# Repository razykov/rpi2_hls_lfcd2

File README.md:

# rpi2_hls_lfcd2
Adapter for connection hls_lfcd2 lidar to RaspberryPi

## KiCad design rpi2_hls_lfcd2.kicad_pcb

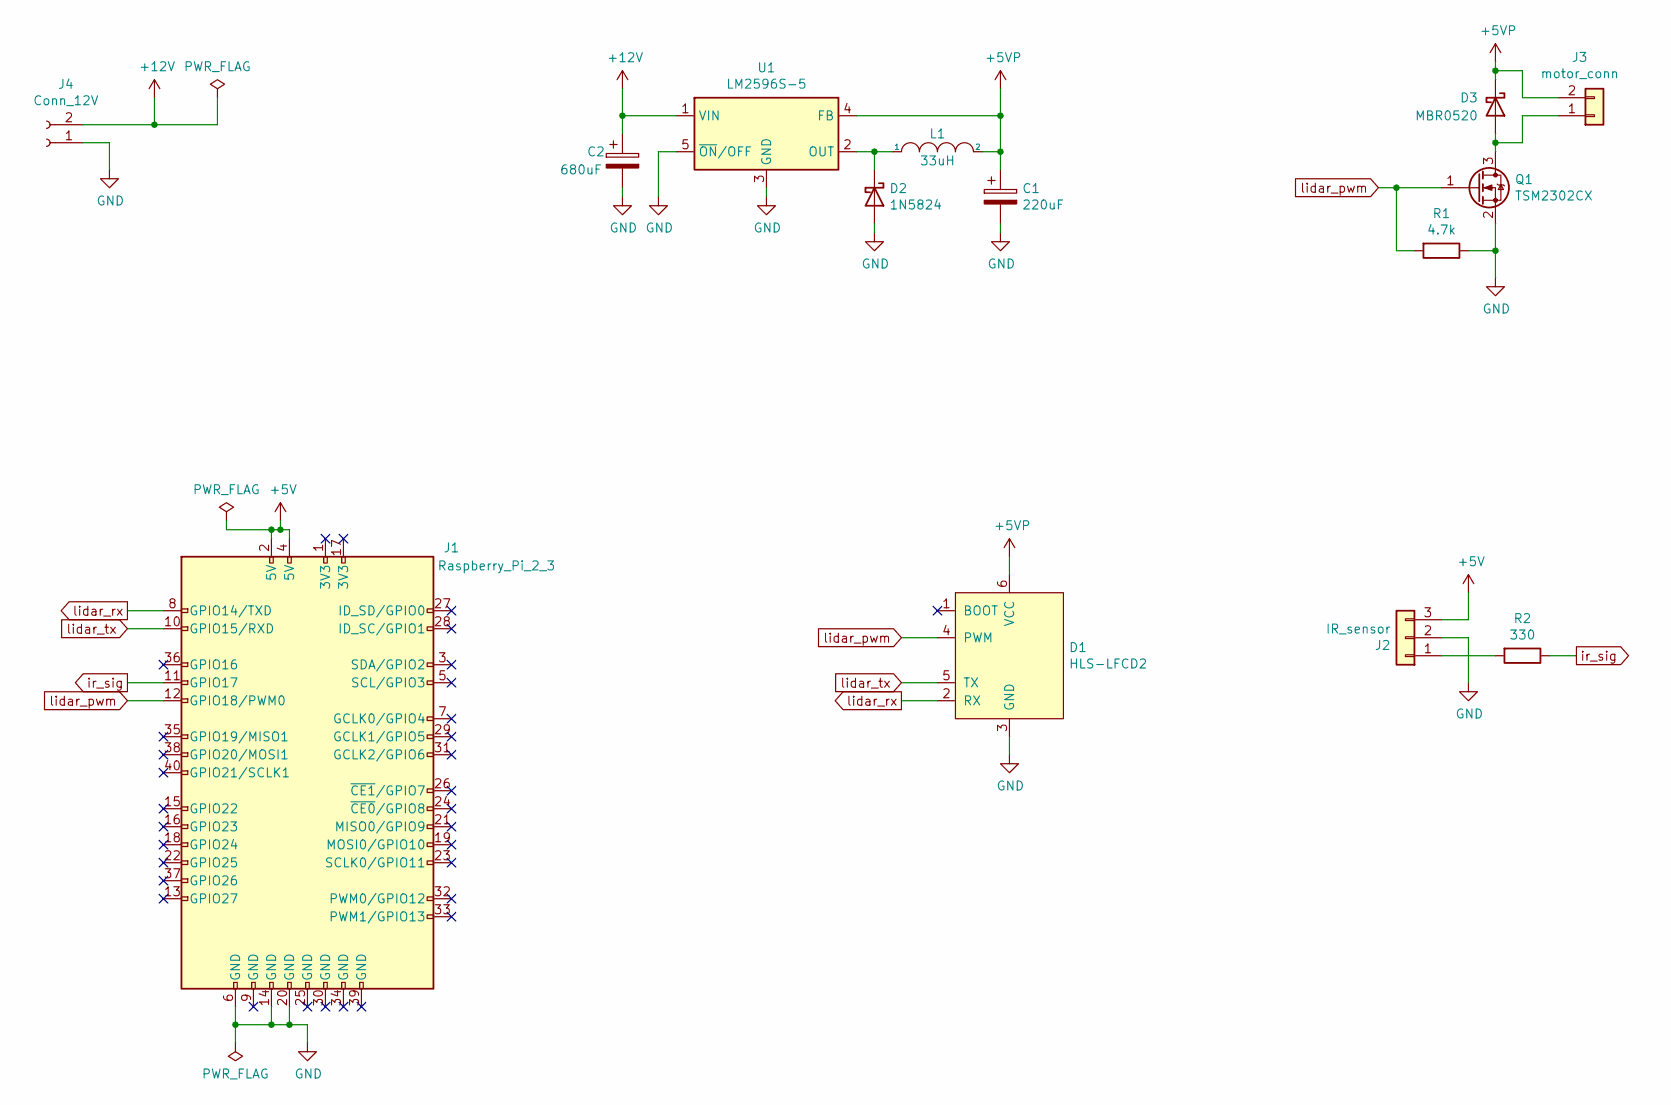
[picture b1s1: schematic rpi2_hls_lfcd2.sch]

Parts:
C1: 220uF; CP_Elec_8x10.5
C2: 680uF; CP_Elec_8x10.5
D1: HLS-LFCD2; JST_GH_SM06B-GHS-TB_1x06-1MP_P1.25mm_Horizontal
D2: 1N5824; D_SMA_Handsoldering
D3: MBR0520; D_SOD-123
J1: Raspberry_Pi_2_3; PinHeader_2x20_P2.54mm_Vertical
J2: IR_sensor; JST_PH_S3B-PH-K_1x03_P2.00mm_Horizontal
J3: motor_conn; JST_PH_B2B-PH-K_1x02_P2.00mm_Vertical
J4: Conn_12V; TestPoint_2Pads_Pitch5.08mm_Drill1.3mm
L1: 33uH; L_7.3x7.3_H4.5
Q1: TSM2302CX; SOT-23
R1: 4.7k; R_0805_2012Metric_Pad1.20x1.40mm_HandSolder
R2: 330; R_0805_2012Metric_Pad1.20x1.40mm_HandSolder
U1: LM2596S-5; TO-263-5_TabPin3

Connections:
+5V: J1.2 (5V), J1.4 (5V), J2.3
+5VP: C1.1, D1.6 (VCC), D3.1 (K), J3.2, L1.2, U1.4 (FB)
+12V: C2.1, J4.2, U1.1 (VIN)
GND: C1.2, C2.2, D1.3 (GND), D1.MP, D2.2 (A), J1.6 (GND), J1.14 (GND), J1.20 (GND), J2.2, J4.1, Q1.2 (S), R1.1, U1.3 (GND), U1.5 (~ON~/OFF)
unnamed: D2.1 (K), L1.1, U1.2 (OUT)
unnamed: D3.2 (A), J3.1, Q1.3 (D)
unnamed: J2.1, R2.2
ir_sig: J1.11 (GPIO17), R2.1
lidar_pwm: D1.4 (PWM), J1.12 (GPIO18/PWM0), Q1.1 (G), R1.2
lidar_rx: D1.2 (RX), J1.8 (GPIO14/TXD)
lidar_tx: D1.5 (TX), J1.10 (GPIO15/RXD)

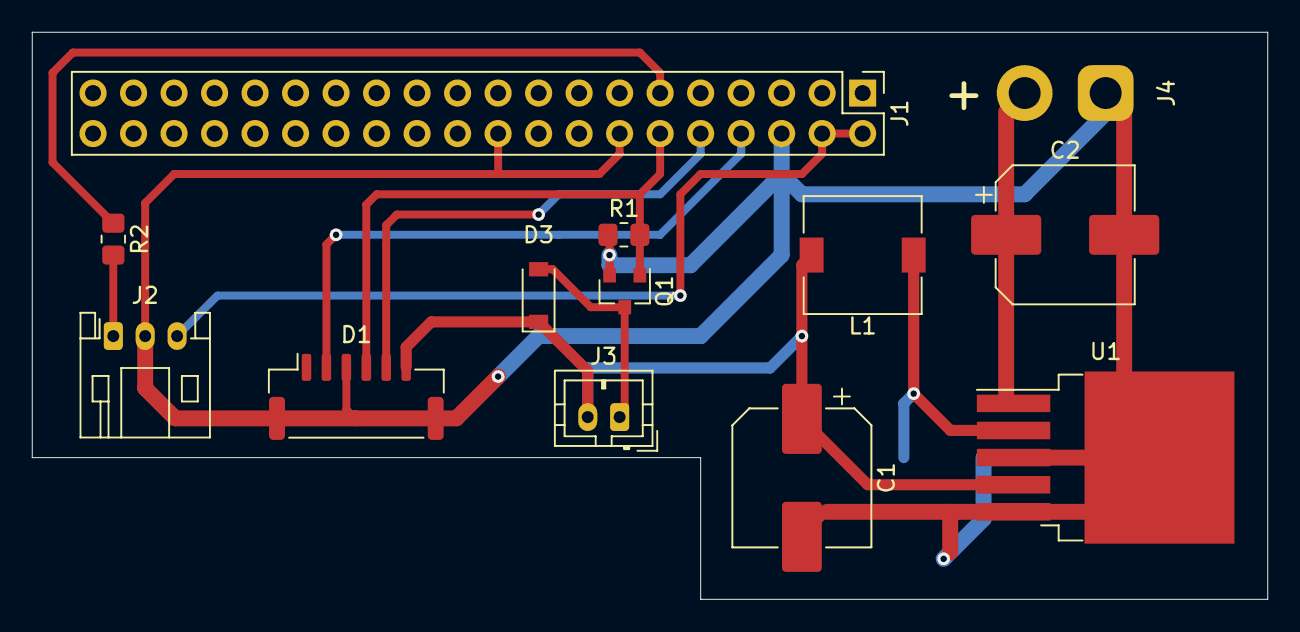
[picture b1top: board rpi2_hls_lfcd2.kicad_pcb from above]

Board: 2 copper layers, 77.5 x 35.6 mm, 14 parts (1 on the bottom side), 11 nets.

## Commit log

2020-12-04 init commit. basic PCB created
2020-12-04 Create README.md
    file:///home/razykov/Pictures/2020-12-04_06-07.png
